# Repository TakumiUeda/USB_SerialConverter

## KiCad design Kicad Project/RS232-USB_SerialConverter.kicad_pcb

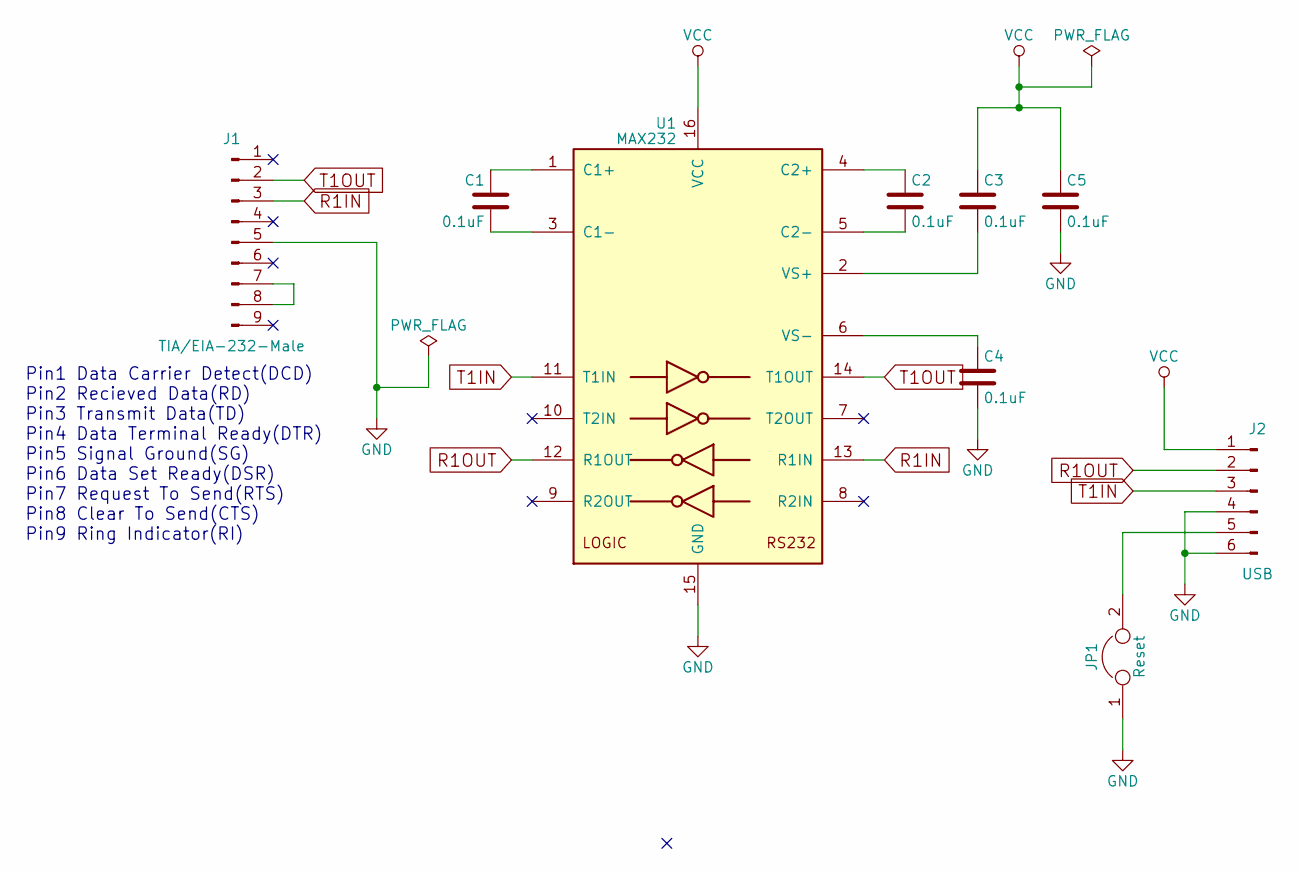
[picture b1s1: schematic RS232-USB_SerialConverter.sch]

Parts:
C1, C2, C3, C4, C5: 0.1uF; C_0603_HandSoldering
J1: TIA/EIA-232-Male; D-SUB Position 9 rightangle
J2: USB; Pin_Header_Straight_1x06_Pitch2.54mm
JP1: Reset; Pin_Header_Straight_1x02_Pitch2.54mm
U1: MAX232; SOIC-16W_5.3x10.2mm_Pitch1.27mm

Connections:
GND: C4.2, C5.2, J1.5, J2.4, J2.6, JP1.1, U1.15 (GND)
unnamed: C1.1, U1.1 (C1+)
unnamed: C1.2, U1.3 (C1-)
unnamed: C2.1, U1.4 (C2+)
unnamed: C2.2, U1.5 (C2-)
unnamed: C3.2, U1.2 (VS+)
unnamed: C4.1, U1.6 (VS-)
unnamed: J1.7, J1.8
unnamed: J2.5, JP1.2
R1IN: J1.3, U1.13 (R1IN)
R1OUT: J2.2, U1.12 (R1OUT)
T1IN: J2.3, U1.11 (T1IN)
T1OUT: J1.2, U1.14 (T1OUT)
VCC: C3.1, C5.1, J2.1, U1.16 (VCC)

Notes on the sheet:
Pin1 Data Carrier Detect(DCD) Pin2 Recieved Data(RD) Pin3 Transmit Data(TD) Pin4 Data Terminal Ready(DTR) Pin5 Signal Ground(SG) Pin6 Data Set Ready(DSR) Pin7 Request To Send(RTS) Pin8 Clear To Send(CTS) Pin9 Ring Indicator(RI)

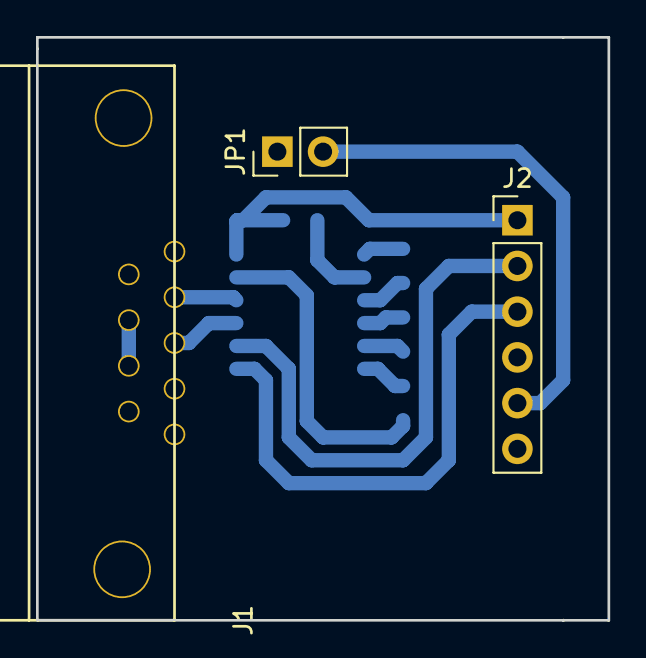
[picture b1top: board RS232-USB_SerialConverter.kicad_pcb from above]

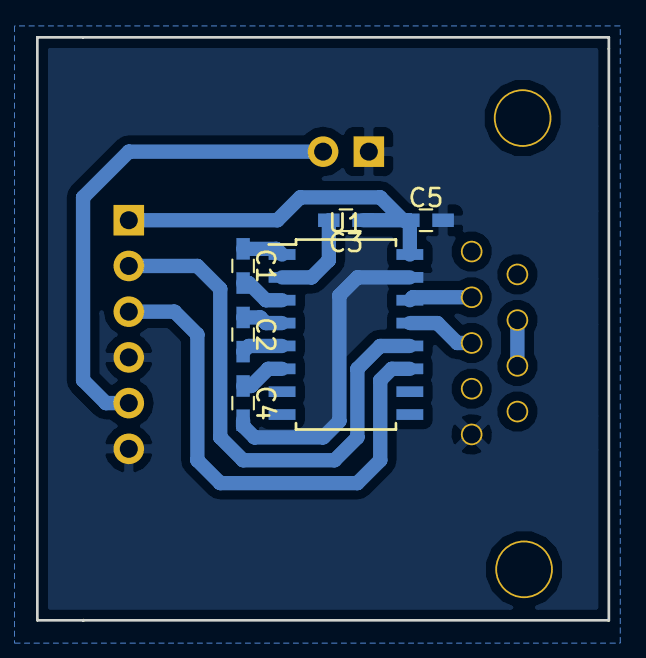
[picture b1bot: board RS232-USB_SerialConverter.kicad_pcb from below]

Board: 2 copper layers, 31.8 x 32.4 mm, 9 parts (6 on the bottom side), 14 nets.

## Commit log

2018-06-14 add sch
2018-06-14 add LICENSE
2018-06-15 add text
2018-06-15 add folder
2018-06-16 add pcb
2018-06-16 add plot
